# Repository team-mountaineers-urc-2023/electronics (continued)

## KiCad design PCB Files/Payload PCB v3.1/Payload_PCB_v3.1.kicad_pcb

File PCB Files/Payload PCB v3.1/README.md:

# Payload PCB v3.1

## Overview
The Payload PCB is used to control the electronics on the manipulator and the science payload. It can control up to eight DC motors and twelve servos. It also includes the hardware necessary for CAN bus communication, extra I/O connectors, payload select signals, and a USB2CAN converter.

## Features
- 4-layer board
- Raspberry Pi Pico microcontroller
- 4 DRV8874 H-bridge motor driver breakout boards capable of controlling 12V motors
- 2 TB6612FNG motor driver breakout boards that can each control two 12V motors or one stepper motor
- Capable of controlling up to twelve servo motors with selectable power output
- Hardware for CAN bus communication
- Optional place to put a 16th brick 12V regulator to power the board and payload motors
- 17 I/O connectors with GPIO, PWM, and/or analog input capabilities
- Payload select pins and LEDS to indicate which payload is plugged in
- Integrated USB2CAN converter which allows the computer to connect to the CAN bus using a USB connection
- Reverse polarity protection

## Contributors
- [Zach Waddell](https://github.com/zmw0006)

- [Ronald Butts](https://github.com/rmb0034)

- [Kendra Gillo](https://github.com/kgillo)

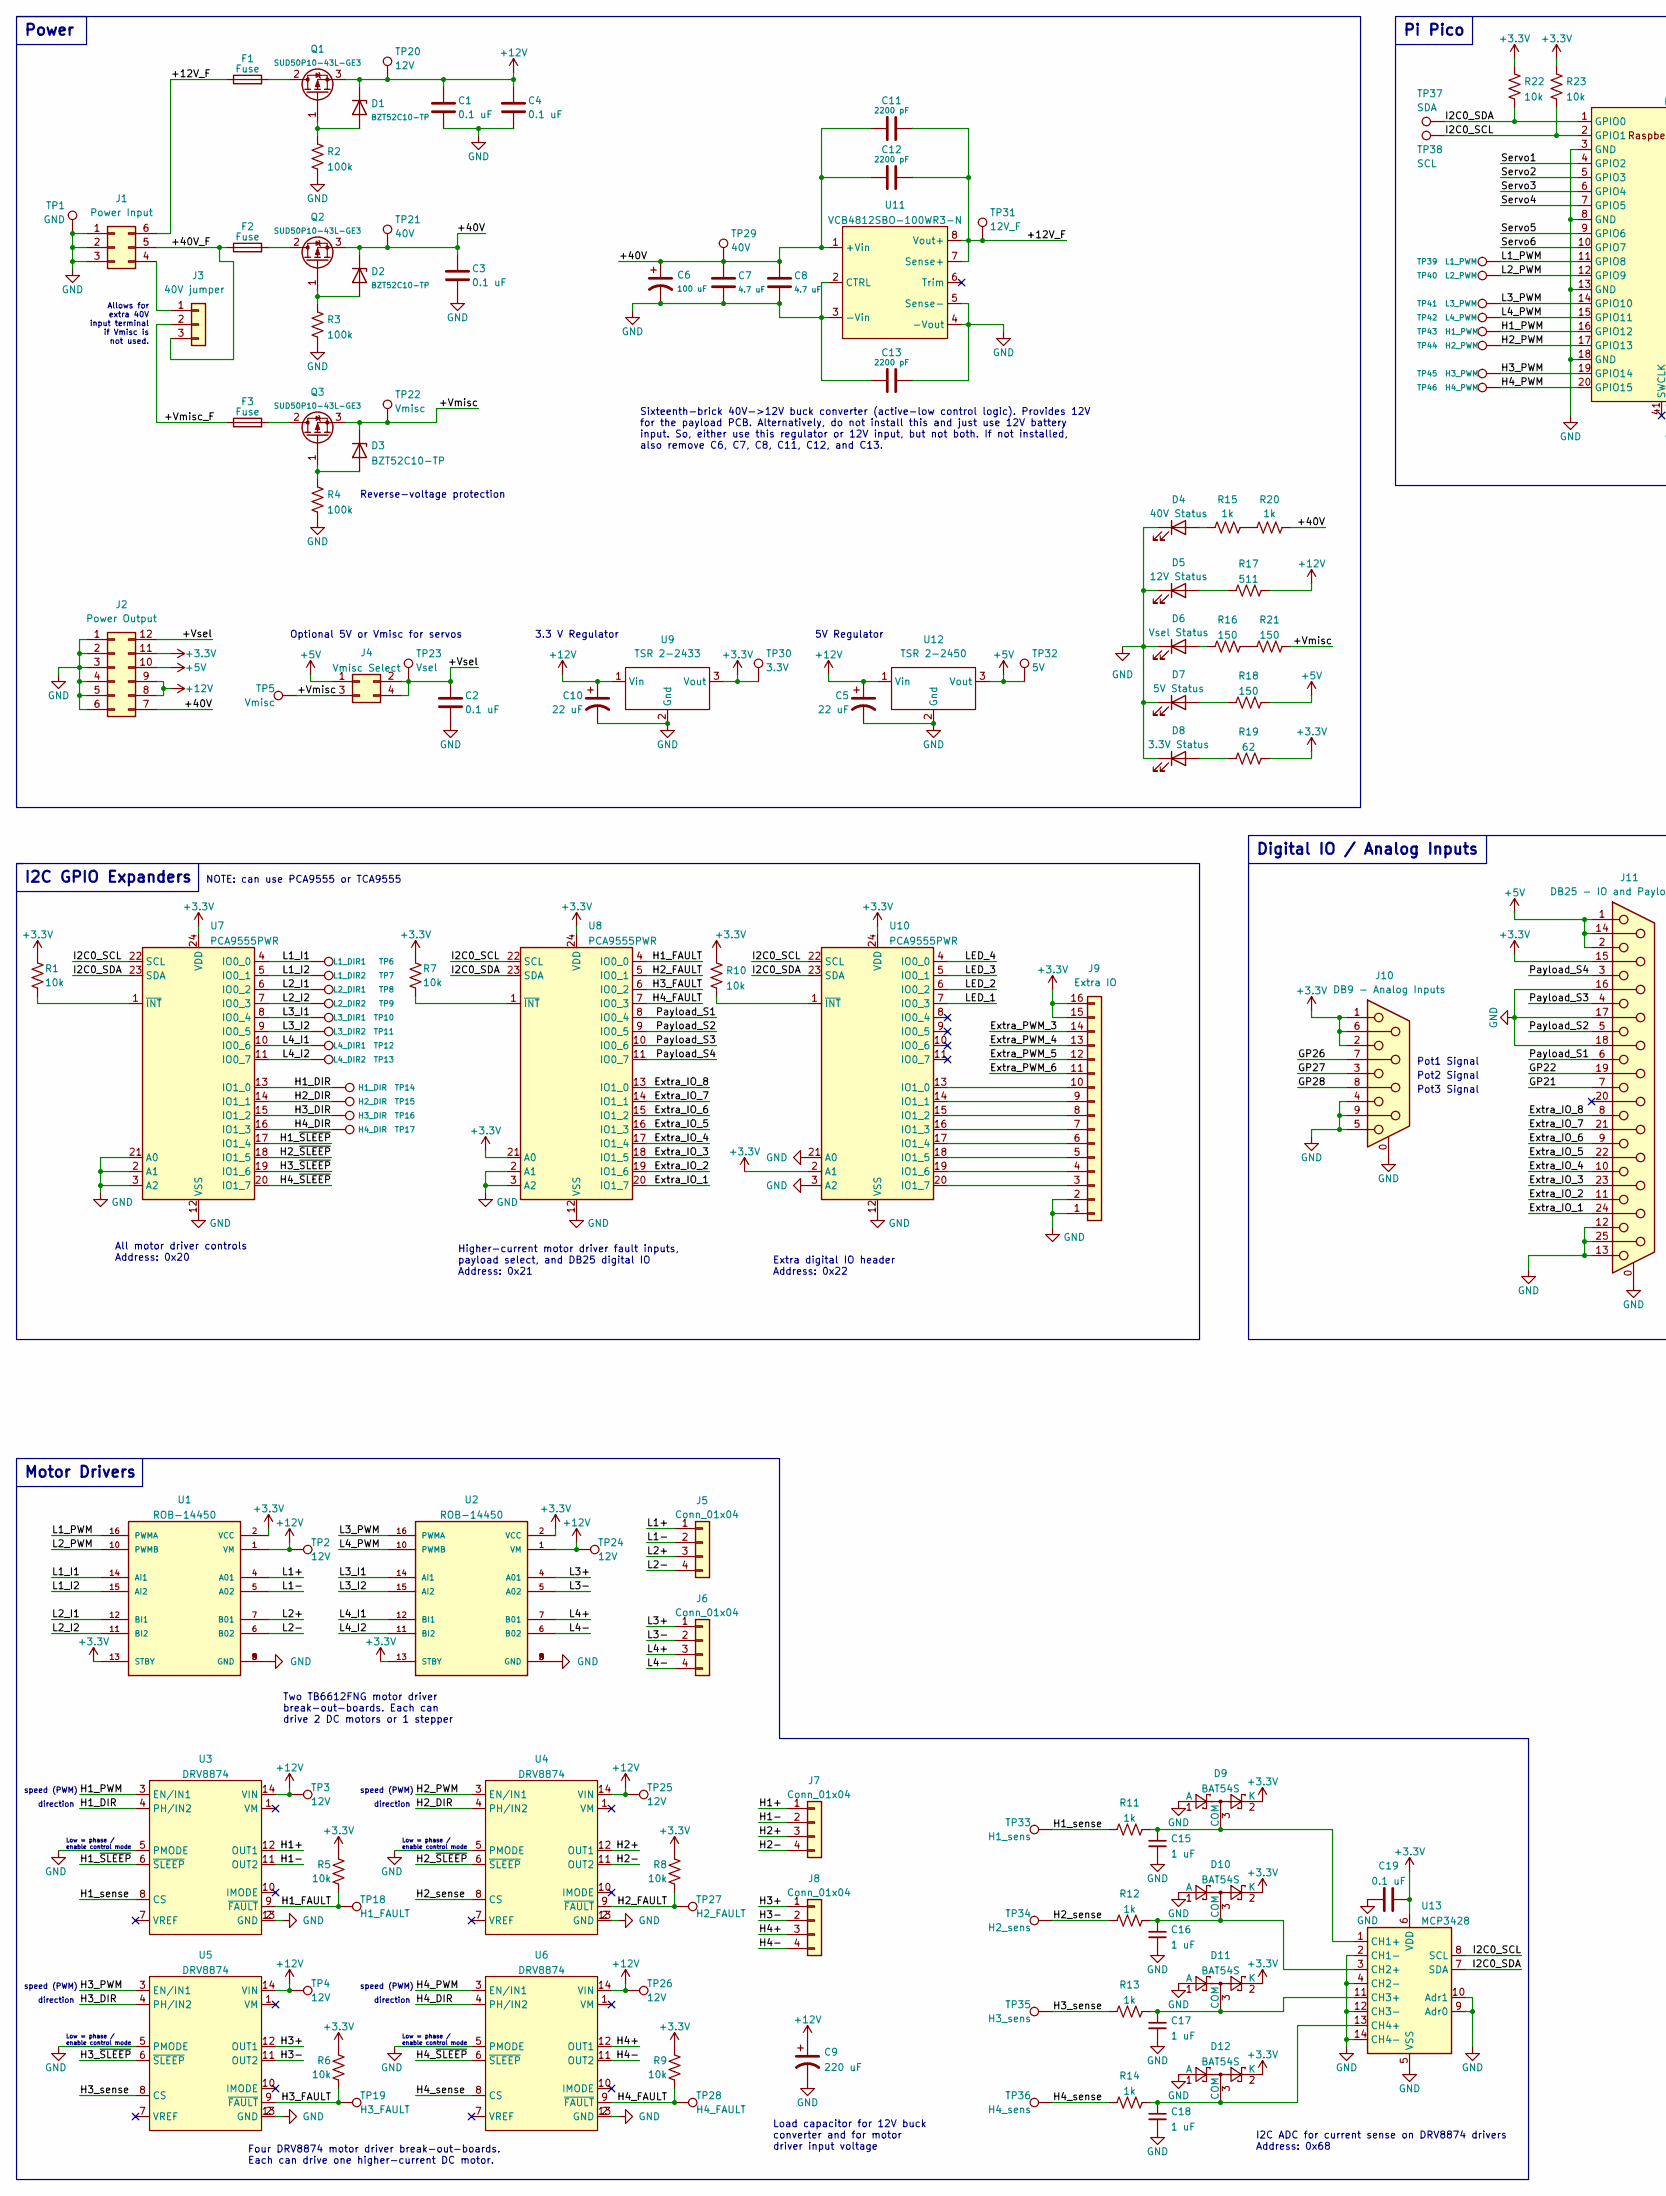
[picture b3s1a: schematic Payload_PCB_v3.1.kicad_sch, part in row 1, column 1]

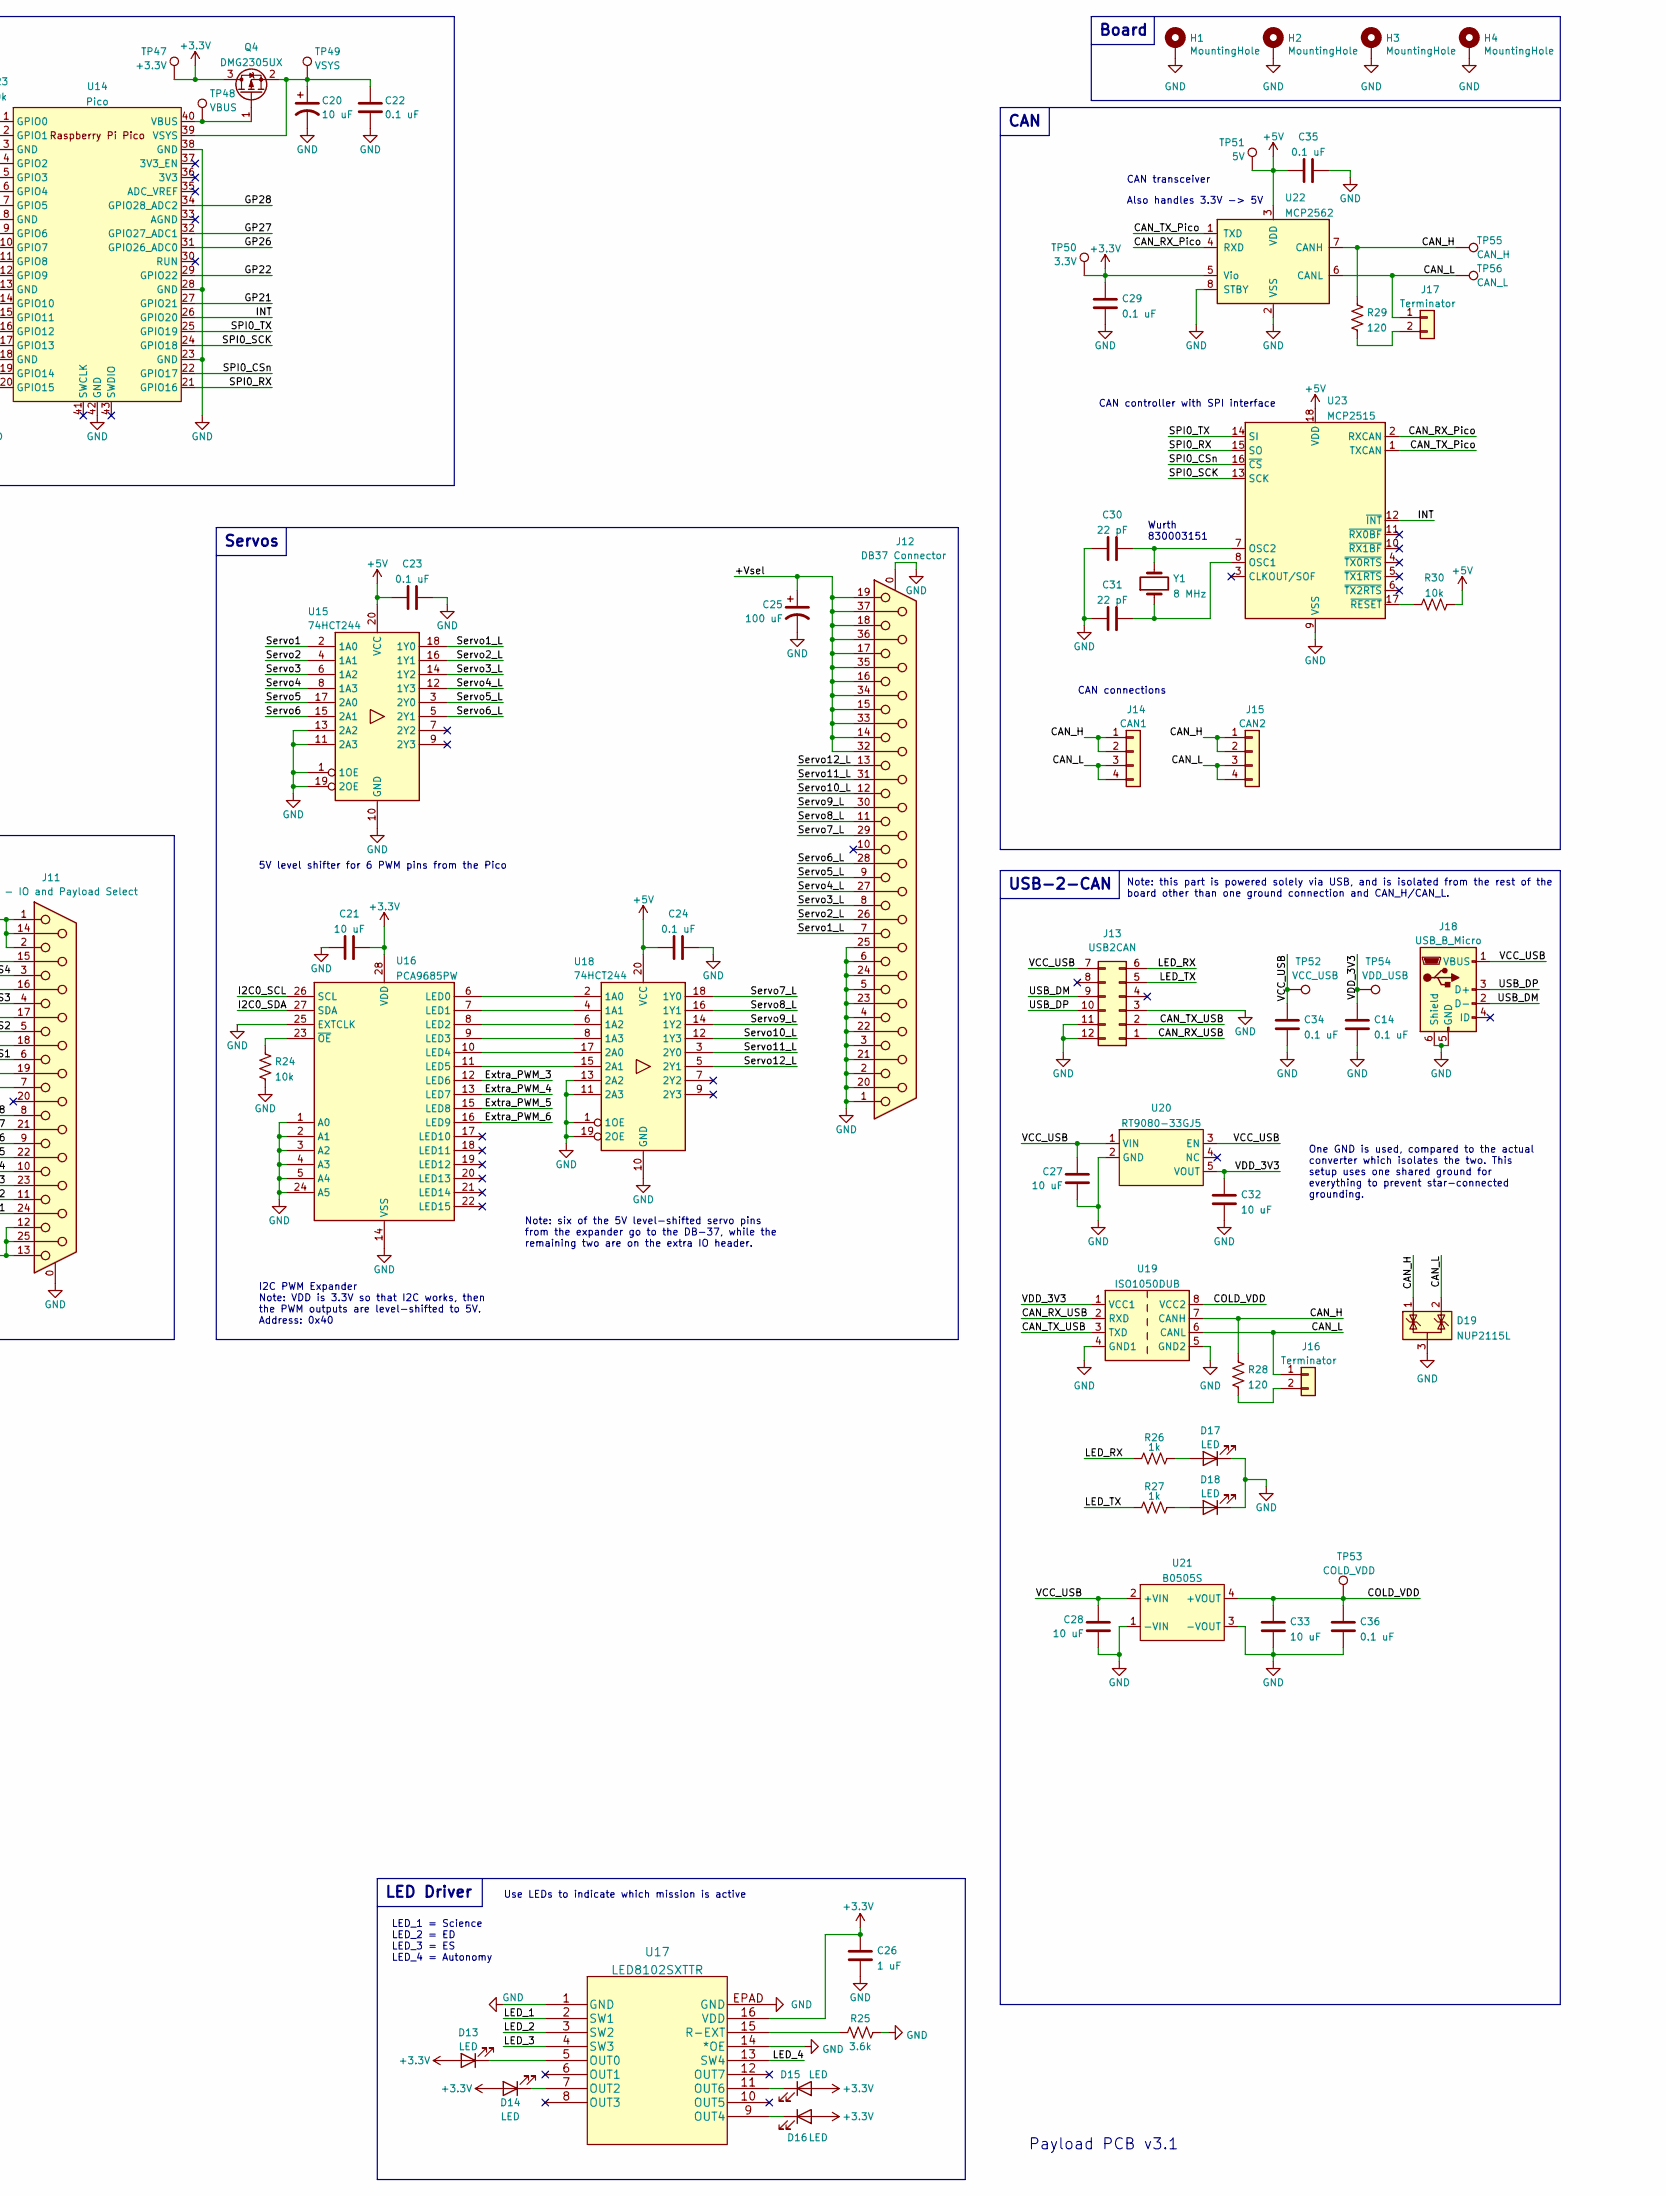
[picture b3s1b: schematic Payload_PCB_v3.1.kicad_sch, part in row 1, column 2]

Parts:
C1, C2, C3, C4, C14, C19, C22, C23, C24, C29, C34, C35, C36: 0.1 uF; C_1206_3216Metric_Pad1.33x1.80mm_HandSolder
C5, C10: 22 uF; UCM1H220MCL1GS
C6, C25: 100 uF; CP_Radial_D10.0mm_P5.00mm
C7, C8: 4.7 uF; C_1206_3216Metric_Pad1.33x1.80mm_HandSolder
C9: 220 uF; CP_Radial_D10.0mm_P5.00mm
C11, C12, C13: 2200 pF; C_1206_3216Metric_Pad1.33x1.80mm_HandSolder
C15, C16, C17, C18, C26: 1 uF; C_1206_3216Metric_Pad1.33x1.80mm_HandSolder
C20: 10 uF; UCM1H220MCL1GS
C21, C27, C28, C32, C33: 10 uF; C_1206_3216Metric_Pad1.33x1.80mm_HandSolder
C30, C31: 22 pF; C_0603_1608Metric_Pad1.08x0.95mm_HandSolder
D1, D2, D3: BZT52C10-TP; D_SOD-123
D4: 40V Status; LED_0805_2012Metric_Pad1.15x1.40mm_HandSolder
D5: 12V Status; LED_0805_2012Metric_Pad1.15x1.40mm_HandSolder
D6: Vsel Status; LED_0805_2012Metric_Pad1.15x1.40mm_HandSolder
D7: 5V Status; LED_0805_2012Metric_Pad1.15x1.40mm_HandSolder
D8: 3.3V Status; LED_0805_2012Metric_Pad1.15x1.40mm_HandSolder
D9, D10, D11, D12: BAT54S; SOT-23
D13, D14, D15, D16, D17, D18: LED; LED_0805_2012Metric_Pad1.15x1.40mm_HandSolder
D19: NUP2115L; SOT-23
F1, F2, F3: Fuse; Fuseholder_Blade_Mini_Keystone_3568
H1, H2, H3, H4: MountingHole; MountingHole_3.2mm_M3_DIN965_Pad
J1: Power Input; Molex_Mini-Fit_Jr_5569-06A2_2x03_P4.20mm_Horizontal
J2: Power Output; Molex_Mini-Fit_Jr_5569-12A2_2x06_P4.20mm_Horizontal
J3: 40V jumper; 3_Wire_Jumper
J4: Vmisc Select; PinHeader_2x02_P2.54mm_Vertical
J5, J6, J7, J8: Conn_01x04; PhoenixContact_MCV_1,5_4-G-3.5_1x04_P3.50mm_Vertical
J9: Extra IO; PinSocket_2x08_P2.54mm_Vertical
J10: DB9 - Analog Inputs; DSUB-9_Female_Vertical_P2.77x2.84mm_MountingHoles
J11: DB25 - IO and Payload Select; DSUB-25_Female_Vertical_P2.77x2.84mm_MountingHoles
J12: DB37 Connector; DSUB-37_Female_Vertical_P2.77x2.84mm_MountingHoles
J13: USB2CAN; USB_2_CAN_Headers
J14: CAN1; 2604-3102
J15: CAN2; 2604-3102
J16, J17: Terminator; PinHeader_1x02_P2.54mm_Vertical
J18: USB_B_Micro; USB_Micro-B_Molex-105017-0001
Q1, Q2, Q3: SUD50P10-43L-GE3; TO-252-2
Q4: DMG2305UX; SOT-23
R1, R5, R6, R7, R8, R9, R10, R22, R23, R24, R30: 10k; R_0805_2012Metric_Pad1.20x1.40mm_HandSolder
R2, R3, R4: 100k; R_0805_2012Metric_Pad1.20x1.40mm_HandSolder
R11, R12, R13, R14, R15, R20, R26, R27: 1k; R_0805_2012Metric_Pad1.20x1.40mm_HandSolder
R16, R18, R21: 150; R_0805_2012Metric_Pad1.20x1.40mm_HandSolder
R17: 511; R_0805_2012Metric_Pad1.20x1.40mm_HandSolder
R19: 62; R_0805_2012Metric_Pad1.20x1.40mm_HandSolder
R25: 3.6k; R_0805_2012Metric_Pad1.20x1.40mm_HandSolder
R28, R29: 120; R_0805_2012Metric_Pad1.20x1.40mm_HandSolder
TP1: GND; TestPoint_THTPad_1.5x1.5mm_Drill0.7mm
TP2, TP3, TP4, TP24, TP25, TP26: 12V; TestPoint_THTPad_1.0x1.0mm_Drill0.5mm
TP5: Vmisc; TestPoint_THTPad_1.5x1.5mm_Drill0.7mm
TP6: L1_DIR1; TestPoint_Pad_1.5x1.5mm
TP7: L1_DIR2; TestPoint_Pad_1.5x1.5mm
TP8: L2_DIR1; TestPoint_Pad_1.5x1.5mm
TP9: L2_DIR2; TestPoint_Pad_1.5x1.5mm
TP10: L3_DIR1; TestPoint_Pad_1.5x1.5mm
TP11: L3_DIR2; TestPoint_Pad_1.5x1.5mm
TP12: L4_DIR1; TestPoint_Pad_1.5x1.5mm
TP13: L4_DIR2; TestPoint_Pad_1.5x1.5mm
TP14: H1_DIR; TestPoint_Pad_1.5x1.5mm
TP15: H2_DIR; TestPoint_Pad_1.5x1.5mm
TP16: H3_DIR; TestPoint_Pad_1.5x1.5mm
TP17: H4_DIR; TestPoint_Pad_1.5x1.5mm
TP18: H1_FAULT; TestPoint_Pad_1.5x1.5mm
TP19: H3_FAULT; TestPoint_Pad_1.5x1.5mm
TP20: 12V; TestPoint_Pad_1.5x1.5mm
TP21: 40V; TestPoint_Pad_1.5x1.5mm
TP22: Vmisc; TestPoint_Pad_1.5x1.5mm
TP23: Vsel; TestPoint_THTPad_1.5x1.5mm_Drill0.7mm
TP27: H2_FAULT; TestPoint_Pad_1.5x1.5mm
TP28: H4_FAULT; TestPoint_Pad_1.5x1.5mm
TP29: 40V; TestPoint_THTPad_1.5x1.5mm_Drill0.7mm
TP30, TP50: 3.3V; TestPoint_THTPad_1.5x1.5mm_Drill0.7mm
TP31: 12V_F; TestPoint_THTPad_1.5x1.5mm_Drill0.7mm
TP32, TP51: 5V; TestPoint_THTPad_1.5x1.5mm_Drill0.7mm
TP33: H1_sens; TestPoint_Pad_1.5x1.5mm
TP34: H2_sens; TestPoint_Pad_1.5x1.5mm
TP35: H3_sens; TestPoint_Pad_1.5x1.5mm
TP36: H4_sens; TestPoint_Pad_1.5x1.5mm
TP37: SDA; TestPoint_THTPad_1.5x1.5mm_Drill0.7mm
TP38: SCL; TestPoint_THTPad_1.5x1.5mm_Drill0.7mm
TP39: L1_PWM; TestPoint_Pad_1.5x1.5mm
TP40: L2_PWM; TestPoint_Pad_1.5x1.5mm
TP41: L3_PWM; TestPoint_Pad_1.5x1.5mm
TP42: L4_PWM; TestPoint_Pad_1.5x1.5mm
TP43: H1_PWM; TestPoint_Pad_1.5x1.5mm
TP44: H2_PWM; TestPoint_Pad_1.5x1.5mm
TP45: H3_PWM; TestPoint_Pad_1.5x1.5mm
TP46: H4_PWM; TestPoint_Pad_1.5x1.5mm
TP47: +3.3V; TestPoint_THTPad_1.5x1.5mm_Drill0.7mm
TP48: VBUS; TestPoint_THTPad_1.5x1.5mm_Drill0.7mm
TP49: VSYS; TestPoint_THTPad_1.5x1.5mm_Drill0.7mm
TP52: VCC_USB; TestPoint_THTPad_1.5x1.5mm_Drill0.7mm
TP53: COLD_VDD; TestPoint_THTPad_1.5x1.5mm_Drill0.7mm
TP54: VDD_USB; TestPoint_THTPad_1.5x1.5mm_Drill0.7mm
TP55: CAN_H; TestPoint_THTPad_1.5x1.5mm_Drill0.7mm
TP56: CAN_L; TestPoint_THTPad_1.5x1.5mm_Drill0.7mm
U1, U2: ROB-14450; MODULE_ROB-14450; PARTREV 11-13-17
U3, U4, U5, U6: DRV8874
U7, U8, U10: PCA9555PWR; TSSOP-24_4.4x7.8mm_P0.65mm
U9: TSR 2-2433; CONV_TSR_2-2433
U11: VCB4812SBO-100WR3-N; VCB4812SBO-100WFR3-N
U12: TSR 2-2450; CONV_TSR_2-2433
U13: MCP3428; SOIC-14_3.9x8.7mm_P1.27mm
U14: Pico; RPi_Pico_SMD_TH
U15, U18: 74HCT244; SO-20_12.8x7.5mm_P1.27mm
U16: PCA9685PW; TSSOP-28_4.4x9.7mm_P0.65mm
U17: LED8102SXTTR
U19: ISO1050DUB; SOP-8_6.62x9.15mm_P2.54mm
U20: RT9080-33GJ5; SOT-23-5_HandSoldering
U21: B0505S; CONV_B0505S-1WR3
U22: MCP2562; SOIC-8_3.9x4.9mm_P1.27mm
U23: MCP2515; SOIC-18W_7.5x11.6mm_P1.27mm
Y1: 8 MHz; Crystal_SMD_HC49-SD

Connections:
+3V3: C19.2, C21.2, C26.1, C29.1, D9.2 (K), D10.2 (K), D11.2 (K), D12.2 (K), D13.2 (A), D14.2 (A), D15.2 (A), D16.2 (A), J2.11, J9.15, J9.16, J10.1, J10.2, J10.6, J11.15, Q4.3 (D), R1.2, R5.1, R6.1, R7.2, R8.1, R9.1, R10.2, R19.2, R22.2, R23.2, TP30.1, TP47.1, TP50.1, U1.2 (VCC), U1.13 (STBY), U2.2 (VCC), U2.13 (STBY), U7.24 (VDD), U8.21 (A0), U8.24 (VDD), U9.3 (Vout), U10.2 (A1), U10.24 (VDD), U13.6 (VDD), U16.28 (VDD), U17.16 (VDD), U22.5 (Vio)
+5V: C23.1, C24.1, C35.1, J2.10, J4.1, J11.1, J11.2, J11.14, R18.2, R30.2, TP32.1, TP51.1, U12.3 (Vout), U15.20 (VCC), U18.20 (VCC), U22.3 (VDD), U23.18 (VDD)
+12V: C1.2, C4.2, C5.1, C9.1, C10.1, D1.1 (K), J2.8, J2.9, Q1.3 (S), R17.2, TP2.1, TP3.1, TP4.1, TP20.1, TP24.1, TP25.1, TP26.1, U1.1 (VM), U2.1 (VM), U3.14 (VIN), U4.14 (VIN), U5.14 (VIN), U6.14 (VIN), U9.1 (Vin), U12.1 (Vin)
/+12V_F: C11.2, C12.2, F1.1, J1.6, TP31.1, U11.7 (Sense+), U11.8 (Vout+)
/+40V: C3.2, C6.1, C7.1, C8.1, C11.1, C12.1, D2.1 (K), J2.7, Q2.3 (S), R20.2, TP21.1, TP29.1, U11.1 (+Vin)
/+40V_F: F2.1, J1.5, J3.3
/+Vmisc: D3.1 (K), J4.3, Q3.3 (S), R21.2, TP5.1, TP22.1
/+Vmisc_F: F3.1, J3.2
/+Vsel: C2.2, C25.1, J2.12, J4.2, J4.4, J12.14, J12.15, J12.16, J12.17, J12.18, J12.19, J12.32, J12.33, J12.34, J12.35, J12.36, J12.37, TP23.1
/CAN_H: D19.1 (K), J14.1, J14.2, J15.1, J15.2, R28.2, R29.2, TP55.1, U19.7 (CANH), U22.7 (CANH)
/CAN_L: D19.2 (K), J14.3, J14.4, J15.3, J15.4, J16.1, J17.1, TP56.1, U19.6 (CANL), U22.6 (CANL)
/CAN_RX_Pico: U22.4 (RXD), U23.2 (RXCAN)
/CAN_RX_USB: J13.1, U19.2 (RXD)
/CAN_TX_Pico: U22.1 (TXD), U23.1 (TXCAN)
/CAN_TX_USB: J13.2, U19.3 (TXD)
/COLD_VDD: C33.1, C36.1, TP53.1, U19.8 (VCC2), U21.4 (+VOUT)
/Extra_IO_1: J11.24, U8.20 (IO1_7)
/Extra_IO_2: J11.11, U8.19 (IO1_6)
/Extra_IO_3: J11.23, U8.18 (IO1_5)
/Extra_IO_4: J11.10, U8.17 (IO1_4)
/Extra_IO_5: J11.22, U8.16 (IO1_3)
/Extra_IO_6: J11.9, U8.15 (IO1_2)
/Extra_IO_7: J11.21, U8.14 (IO1_1)
/Extra_IO_8: J11.8, U8.13 (IO1_0)
/Extra_PWM_3: J9.14, U16.12 (LED6)
/Extra_PWM_4: J9.13, U16.13 (LED7)
/Extra_PWM_5: J9.12, U16.15 (LED8)
/Extra_PWM_6: J9.11, U16.16 (LED9)
/GP21: J11.7, U14.27 (GPIO21)
/GP22: J11.19, U14.29 (GPIO22)
/GP26: J10.7, U14.31 (GPIO26_ADC0)
/GP27: J10.3, U14.32 (GPIO27_ADC1)
/GP28: J10.8, U14.34 (GPIO28_ADC2)
/H1+: J7.1, U3.12 (OUT1)
/H1-: J7.2, U3.11 (OUT2)
/H1_DIR: TP14.1, U3.4 (PH/IN2), U7.13 (IO1_0)
/H1_FAULT: R5.2, TP18.1, U3.9 (~FAULT), U8.4 (IO0_0)
/H1_PWM: TP43.1, U3.3 (EN/IN1), U14.16 (GPIO12)
/H1_sense: R11.1, TP33.1, U3.8 (CS)
/H1_~SLEEP: U3.6 (~SLEEP), U7.17 (IO1_4)
/H2+: J7.3, U4.12 (OUT1)
/H2-: J7.4, U4.11 (OUT2)
/H2_DIR: TP15.1, U4.4 (PH/IN2), U7.14 (IO1_1)
/H2_FAULT: R8.2, TP27.1, U4.9 (~FAULT), U8.5 (IO0_1)
/H2_PWM: TP44.1, U4.3 (EN/IN1), U14.17 (GPIO13)
/H2_sense: R12.1, TP34.1, U4.8 (CS)
/H2_~SLEEP: U4.6 (~SLEEP), U7.18 (IO1_5)
/H3+: J8.1, U5.12 (OUT1)
/H3-: J8.2, U5.11 (OUT2)
/H3_DIR: TP16.1, U5.4 (PH/IN2), U7.15 (IO1_2)
/H3_FAULT: R6.2, TP19.1, U5.9 (~FAULT), U8.6 (IO0_2)
/H3_PWM: TP45.1, U5.3 (EN/IN1), U14.19 (GPIO14)
/H3_sense: R13.1, TP35.1, U5.8 (CS)
/H3_~SLEEP: U5.6 (~SLEEP), U7.19 (IO1_6)
/H4+: J8.3, U6.12 (OUT1)
/H4-: J8.4, U6.11 (OUT2)
/H4_DIR: TP17.1, U6.4 (PH/IN2), U7.16 (IO1_3)
/H4_FAULT: R9.2, TP28.1, U6.9 (~FAULT), U8.7 (IO0_3)
/H4_PWM: TP46.1, U6.3 (EN/IN1), U14.20 (GPIO15)
/H4_sense: R14.1, TP36.1, U6.8 (CS)
/H4_~SLEEP: U6.6 (~SLEEP), U7.20 (IO1_7)
/I2C0_SCL: R23.1, TP38.1, U7.22 (SCL), U8.22 (SCL), U10.22 (SCL), U13.8 (SCL), U14.2 (GPIO1), U16.26 (SCL)
/I2C0_SDA: R22.1, TP37.1, U7.23 (SDA), U8.23 (SDA), U10.23 (SDA), U13.7 (SDA), U14.1 (GPIO0), U16.27 (SDA)
/INT: U14.26 (GPIO20), U23.12 (~INT)
/L1+: J5.1, U1.4 (A01)
/L1-: J5.2, U1.5 (A02)
/L1_I1: TP6.1, U1.14 (AI1), U7.4 (IO0_0)
/L1_I2: TP7.1, U1.15 (AI2), U7.5 (IO0_1)
/L1_PWM: TP39.1, U1.16 (PWMA), U14.11 (GPIO8)
/L2+: J5.3, U1.7 (B01)
/L2-: J5.4, U1.6 (B02)
/L2_I1: TP8.1, U1.12 (BI1), U7.6 (IO0_2)
/L2_I2: TP9.1, U1.11 (BI2), U7.7 (IO0_3)
/L2_PWM: TP40.1, U1.10 (PWMB), U14.12 (GPIO9)
/L3+: J6.1, U2.4 (A01)
/L3-: J6.2, U2.5 (A02)
/L3_I1: TP10.1, U2.14 (AI1), U7.8 (IO0_4)
/L3_I2: TP11.1, U2.15 (AI2), U7.9 (IO0_5)
/L3_PWM: TP41.1, U2.16 (PWMA), U14.14 (GPIO10)
/L4+: J6.3, U2.7 (B01)
/L4-: J6.4, U2.6 (B02)
/L4_I1: TP12.1, U2.12 (BI1), U7.10 (IO0_6)
/L4_I2: TP13.1, U2.11 (BI2), U7.11 (IO0_7)
/L4_PWM: TP42.1, U2.10 (PWMB), U14.15 (GPIO11)
/LED_1: U10.7 (IO0_3), U17.2 (SW1)
/LED_2: U10.6 (IO0_2), U17.3 (SW2)
/LED_3: U10.5 (IO0_1), U17.4 (SW3)
/LED_4: U10.4 (IO0_0), U17.13 (SW4)
/LED_RX: J13.6, R26.1
/LED_TX: J13.5, R27.1
/Payload_S1: J11.6, U8.8 (IO0_4)
/Payload_S2: J11.5, U8.9 (IO0_5)
/Payload_S3: J11.4, U8.10 (IO0_6)
/Payload_S4: J11.3, U8.11 (IO0_7)
/SPI0_CSn: U14.22 (GPIO17), U23.16 (~CS)
/SPI0_RX: U14.21 (GPIO16), U23.15 (SO)
/SPI0_SCK: U14.24 (GPIO18), U23.13 (SCK)
/SPI0_TX: U14.25 (GPIO19), U23.14 (SI)
/Servo1: U14.4 (GPIO2), U15.2 (1A0)
/Servo1_L: J12.7, U15.18 (1Y0)
/Servo2: U14.5 (GPIO3), U15.4 (1A1)
/Servo2_L: J12.26, U15.16 (1Y1)
/Servo3: U14.6 (GPIO4), U15.6 (1A2)
/Servo3_L: J12.8, U15.14 (1Y2)
/Servo4: U14.7 (GPIO5), U15.8 (1A3)
/Servo4_L: J12.27, U15.12 (1Y3)
/Servo5: U14.9 (GPIO6), U15.17 (2A0)
/Servo5_L: J12.9, U15.3 (2Y0)
/Servo6: U14.10 (GPIO7), U15.15 (2A1)
/Servo6_L: J12.28, U15.5 (2Y1)
/Servo7_L: J12.29, U18.18 (1Y0)
/Servo8_L: J12.11, U18.16 (1Y1)
/Servo9_L: J12.30, U18.14 (1Y2)
/Servo10_L: J12.12, U18.12 (1Y3)
/Servo11_L: J12.31, U18.3 (2Y0)
/Servo12_L: J12.13, U18.5 (2Y1)
/USB_DM: J13.9, J18.2 (D-)
/USB_DP: J13.10, J18.3 (D+)
/VCC_USB: C27.1, C28.1, C34.1, J13.7, J18.1 (VBUS), TP52.1, U20.1 (VIN), U20.3 (EN), U21.2 (+VIN)
/VDD_3V3: C14.1, C32.1, TP54.1, U19.1 (VCC1), U20.5 (VOUT)
GND: C1.1, C2.1, C3.1, C4.1, C5.2, C6.2, C7.2, C8.2, C9.2, C10.2, C13.1, C13.2, C14.2, C15.2, C16.2, C17.2, C18.2, C19.1, C20.2, C21.1, C22.1, C23.2, C24.2, C25.2, C26.2, C27.2, C28.2, C29.2, C30.1, C31.1, C32.2, C33.2, C34.2, C35.2, C36.2, D4.1 (K), D5.1 (K), D6.1 (K), D7.1 (K), D8.1 (K), D9.1 (A), D10.1 (A), D11.1 (A), D12.1 (A), D17.1 (K), D18.1 (K), D19.3 (A), H1.1, H2.1, H3.1, H4.1, J1.1, J1.2, J1.3, J2.1, J2.2, J2.3, J2.4, J2.5, J2.6, J9.1, J9.2, J10.0 (PAD), J10.4, J10.5, J10.9, J11.0 (PAD), J11.12, J11.13, J11.16, J11.17, J11.18, J11.25, J12.0 (PAD), J12.1, J12.2, J12.3, J12.4, J12.5, J12.6, J12.20, J12.21, J12.22, J12.23, J12.24, J12.25, J13.3, J13.11, J13.12, J18.5 (GND), J18.6 (Shield), R2.2, R3.2, R4.2, R24.1, R25.2, TP1.1, U1.3 (GND), U1.8 (GND), U1.9 (GND), U2.3 (GND), U2.8 (GND), U2.9 (GND), U3.2 (GND), U3.5 (PMODE), U3.13 (GND), U4.2 (GND), U4.5 (PMODE), U4.13 (GND), U5.2 (GND), U5.5 (PMODE), U5.13 (GND), U6.2 (GND), U6.5 (PMODE), U6.13 (GND), U7.2 (A1), U7.3 (A2), U7.12 (VSS), U7.21 (A0), U8.2 (A1), U8.3 (A2), U8.12 (VSS), U9.2 (Gnd), U10.3 (A2), U10.12 (VSS), U10.21 (A0), U11.2 (CTRL), U11.3 (-Vin), U11.4 (-Vout), U11.5 (Sense-), U12.2 (Gnd), U13.2 (CH1-), U13.4 (CH2-), U13.5 (VSS), U13.9 (Adr0), U13.10 (Adr1), U13.12 (CH3-), U13.14 (CH4-), U14.3 (GND), U14.8 (GND), U14.13 (GND), U14.18 (GND), U14.23 (GND), U14.28 (GND), U14.38 (GND), U14.42 (GND), U15.1 (1OE), U15.10 (GND), U15.11 (2A3), U15.13 (2A2), U15.19 (2OE), U16.1 (A0), U16.2 (A1), U16.3 (A2), U16.4 (A3), U16.5 (A4), U16.14 (VSS), U16.24 (A5), U16.25 (EXTCLK), U17.1 (GND), U17.14 (*OE), U17.EPAD (GND), U18.1 (1OE), U18.10 (GND), U18.11 (2A3), U18.13 (2A2), U18.19 (2OE), U19.4 (GND1), U19.5 (GND2), U20.2 (GND), U21.1 (-VIN), U21.3 (-VOUT), U22.2 (VSS), U22.8 (STBY), U23.9 (VSS)
unnamed: C15.1, D9.3 (COM), R11.2, U13.1 (CH1+)
unnamed: C16.1, D10.3 (COM), R12.2, U13.3 (CH2+)
unnamed: C17.1, D11.3 (COM), R13.2, U13.11 (CH3+)
unnamed: C18.1, D12.3 (COM), R14.2, U13.13 (CH4+)
unnamed: C20.1, C22.2, Q4.2 (S), TP49.1, U14.39 (VSYS)
unnamed: C30.2, U23.7 (OSC2), Y1.2
unnamed: C31.2, U23.8 (OSC1), Y1.1
unnamed: D1.2 (A), Q1.1 (G), R2.1
unnamed: D2.2 (A), Q2.1 (G), R3.1
unnamed: D3.2 (A), Q3.1 (G), R4.1
unnamed: D4.2 (A), R15.1
unnamed: D5.2 (A), R17.1
unnamed: D6.2 (A), R16.1
unnamed: D7.2 (A), R18.1
unnamed: D8.2 (A), R19.1
unnamed: D13.1 (K), U17.5 (OUT0)
unnamed: D14.1 (K), U17.7 (OUT2)
unnamed: D15.1 (K), U17.11 (OUT6)
unnamed: D16.1 (K), U17.9 (OUT4)
unnamed: D17.2 (A), R26.2
unnamed: D18.2 (A), R27.2
unnamed: F1.2, Q1.2 (D)
unnamed: F2.2, Q2.2 (D)
unnamed: F3.2, Q3.2 (D)
unnamed: J1.4, J3.1
unnamed: J9.3, U10.20 (IO1_7)
unnamed: J9.4, U10.19 (IO1_6)
unnamed: J9.5, U10.18 (IO1_5)
unnamed: J9.6, U10.17 (IO1_4)
unnamed: J9.7, U10.16 (IO1_3)
unnamed: J9.8, U10.15 (IO1_2)
unnamed: J9.9, U10.14 (IO1_1)
unnamed: J9.10, U10.13 (IO1_0)
unnamed: J16.2, R28.1
unnamed: J17.2, R29.1
unnamed: Q4.1 (G), TP48.1, U14.40 (VBUS)
unnamed: R1.1, U7.1 (~INT)
unnamed: R7.1, U8.1 (~INT)
unnamed: R10.1, U10.1 (~INT)
unnamed: R15.2, R20.1
unnamed: R16.2, R21.1
unnamed: R24.2, U16.23 (~OE)
unnamed: R25.1, U17.15 (R-EXT)
unnamed: R30.1, U23.17 (~RESET)
unnamed: U16.6 (LED0), U18.2 (1A0)
unnamed: U16.7 (LED1), U18.4 (1A1)
unnamed: U16.8 (LED2), U18.6 (1A2)
unnamed: U16.9 (LED3), U18.8 (1A3)
unnamed: U16.10 (LED4), U18.17 (2A0)
unnamed: U16.11 (LED5), U18.15 (2A1)

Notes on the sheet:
direction
speed (PWM)
CAN connections
Low = phase / enable control mode
Payload PCB v3.1
Two TB6612FNG motor driver break-out-boards. Each can drive 2 DC motors or 1 stepper
Allows for extra 40V input terminal if Vmisc is not used.
CAN transceiver
Sixteenth-brick 40V->12V buck converter (active-low control logic). Provides 12V for the payload PCB. Alternatively, do not install this and just use 12V battery input. So, either use this regulator or 12V input, but not both. If not installed, also remove C6, C7, C8, C11, C12, and C13.
Wurth 830003151
Pot2 Signal
Optional 5V or Vmisc for servos
5V Regulator
Board
All motor driver controls Address: 0x20
LED_1 = Science LED_2 = ED LED_3 = ES LED_4 = Autonomy
Load capacitor for 12V buck converter and for motor driver input voltage
One GND is used, compared to the actual converter which isolates the two. This setup uses one shared ground for everything to prevent star-connected grounding.
5V level shifter for 6 PWM pins from the Pico
I2C GPIO Expanders
Higher-current motor driver fault inputs, payload select, and DB25 digital IO Address: 0x21
3.3 V Regulator
Extra digital IO header Address: 0x22
CAN
Power
Pot3 Signal
Reverse-voltage protection
CAN controller with SPI interface
Note: this part is powered solely via USB, and is isolated from the rest of the board other than one ground connection and CAN_H/CAN_L.
Use LEDs to indicate which mission is active
I2C PWM Expander Note: VDD is 3.3V so that I2C works, then the PWM outputs are level-shifted to 5V. Address: 0x40
Pi Pico
USB-2-CAN
Digital IO / Analog Inputs
Note: six of the 5V level-shifted servo pins from the expander go to the DB-37, while the remaining two are on the extra IO header.
Servos
Pot1 Signal
Motor Drivers
NOTE: can use PCA9555 or TCA9555
Also handles 3.3V -> 5V

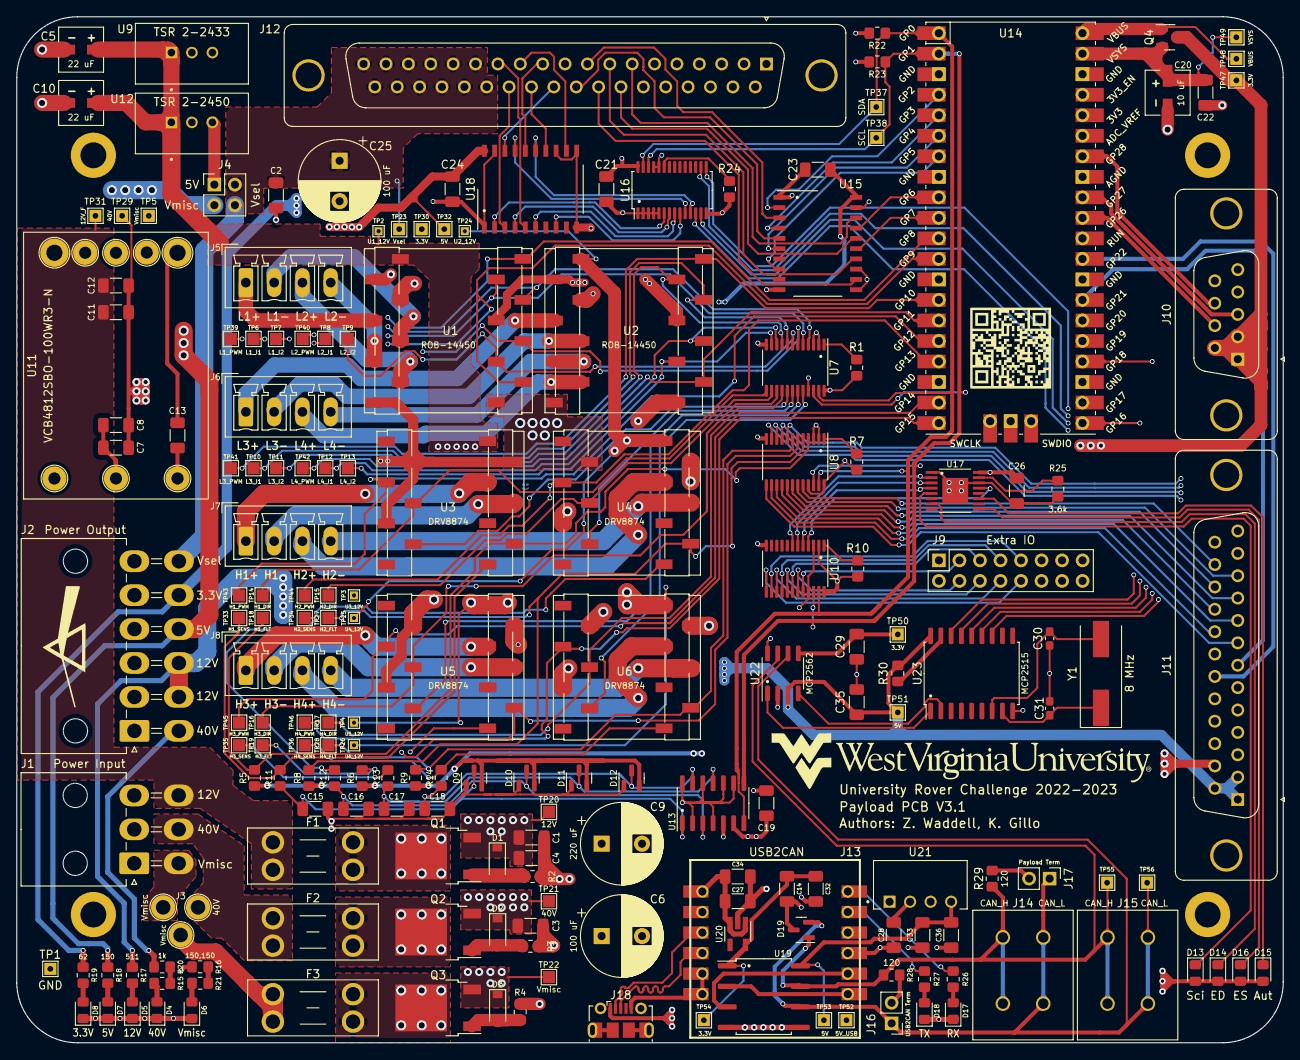
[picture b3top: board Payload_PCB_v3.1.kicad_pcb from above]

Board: 4 copper layers, 156.8 x 127.0 mm, 194 parts (0 on the bottom side), 171 nets.

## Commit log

2023-09-24 Initial public release commit
2023-09-24 Update README.md
    Updated readme to show battery monitor 3D rendering
2023-09-24 Update README.md
    Updated payload PCB readme to include 3D rendering
2023-09-24 Update README.md
    Updated readme to include PDB picture
